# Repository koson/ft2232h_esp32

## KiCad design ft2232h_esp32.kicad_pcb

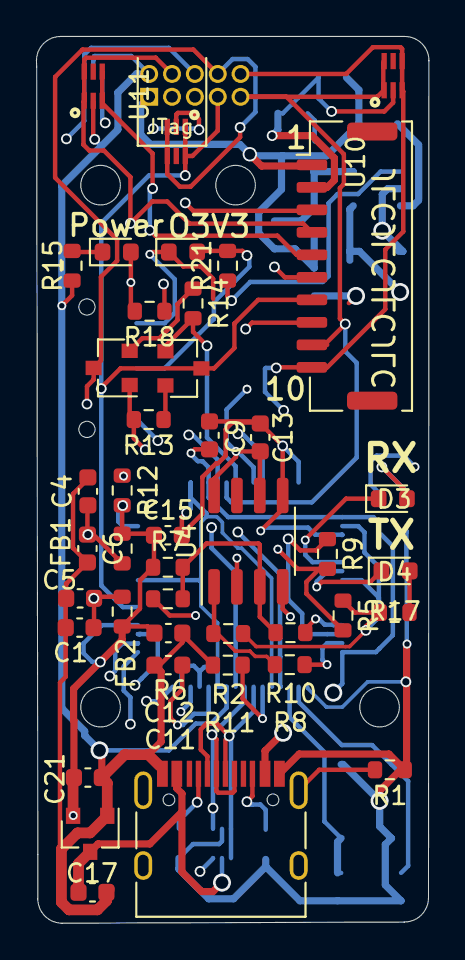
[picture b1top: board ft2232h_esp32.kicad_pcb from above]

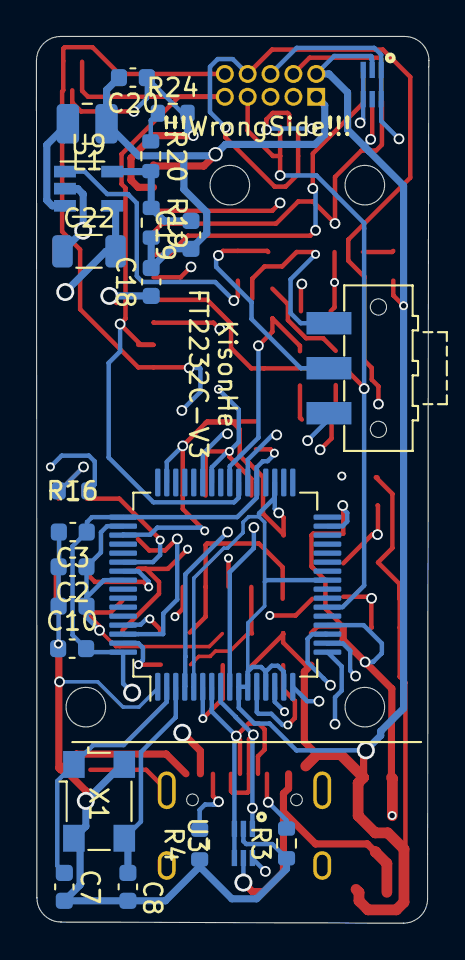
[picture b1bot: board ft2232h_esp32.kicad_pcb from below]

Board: 4 copper layers, 21.8 x 49.3 mm, 70 parts (23 on the bottom side), 46 nets.

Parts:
C1, C2, C3, C4: 4.7uf/25V(10%); C_0603_1608Metric
C5, C6, C9, C10, C11, C12, C13, C14, C15: 0.1uf/25v(10%); C_0603_1608Metric
C7, C8: 20pf; C_0603_1608Metric
C17, C21: 1uf; C_0603_1608Metric
C18, C20: 22uf; C_0603_1608Metric
C19: 22pf; C_0603_1608Metric
C22: 22uf/6.3v; C_1206_3216Metric
D2: POWERLED-Green; LED_0603_1608Metric
D3: BLUELED; LED_0603_1608Metric
D4: REDLED; LED_0603_1608Metric
D5: OUT3V3LED-Yellow; LED_0603_1608Metric
FB1, FB2: 1k@100mhz; R_0603_1608Metric
H1, H2, H3, H4: MountingHole; MountingHole_2.2mm_M2
J1: USB_C_Receptacle_USB2.0; USB_C_Receptacle_HRO_TYPE-C-31-M-12
L1: 2.2uh; L_1008_2520Metric
Q1, Q2: S8050; SOT-23
R1, R24: 0; R_0603_1608Metric
R2, R5, R7: 10k(1%); R_0603_1608Metric
R3, R4: 5.1k; R_0603_1608Metric
R6: 2.2k(1%); R_0603_1608Metric
R8, R9, R10: 33R(1%); R_0603_1608Metric
R11: 12k(1%); R_0603_1608Metric
R12: 1k(1%); R_0603_1608Metric
R13, R14: 100k(1%); R_0603_1608Metric
R15, R21: 10k; R_0603_1608Metric
R16, R17: 2.2k; R_0603_1608Metric
R18: 1k; R_0603_1608Metric
R19: 100k; R_0603_1608Metric
R20: 22k; R_0603_1608Metric
SW1: SW_SPDT; SW_SPDT_CK-JS102011SAQN
U1: ESP32FullConnector; jtag1.27-10
U2: ESP32FullConnector; Molex_CLIK-Mate_502382-1070_1x10-1MP_P1.25mm_Vertical
U3, U10, U11, U12, U13: USBLC6-2SC6-Power_Protection; USBLC6-2P6-SOT666
U4: 93C56-C173182; SOP-8_3.76x4.96mm_P1.27mm
U5: FT2232HL; LQFP-64_10x10mm_P0.5mm
U8: XC6206P332MR; SOT-23
U9: SY8089AAAC; TSOT-23-5
X1: ASCO; Oscillator_SMD_Fordahl_DFAS15-4Pin_5.0x3.2mm

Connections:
3v3OUT: C18.2, C19.1, C20.2, L1.1, R19.2, U1.1, U2.1
2232RX: U1.9, U2.9, U5.39, U10.1, U10.6
2232TX: U1.10, U2.10, U5.38, U10.3, U10.4
+1V8: C3.1, C9.1, C10.1, C11.1, U5.12, U5.37, U5.49, U5.64
+3V3: C2.1, C12.1, C13.1, C14.1, C15.1, C21.2, D2.2, FB1.2, FB2.2, R2.1, R5.1, R7.1, R12.2, R16.1, R17.1, R18.2, U4.6, U4.8, U5.20, U5.31, U5.42, U5.50, U5.56, U8.2
EECLK: R5.2, R9.2, U4.2
EECS: R2.2, R8.2, U4.1
EEDATA: R6.1, R7.2, R10.2, U4.3
GND: C1.2, C2.2, C3.2, C4.2, C5.2, C6.2, C7.2, C8.2, C9.2, C10.2, C11.2, C12.2, C13.2, C14.2, C15.2, C17.1, C18.1, C20.1, C21.1, C22.1, D5.1, J1.A1, J1.A12, J1.B1, J1.B12, R1.1, R3.1, R4.1, R11.2, R15.1, R24.2, SW1.3, U1.2, U2.2, U3.2, U4.5, U5.1, U5.5, U5.10, U5.11, U5.13, U5.15, U5.25, U5.35, U5.47, U5.51, U8.1, U9.2, U10.2, U11.2, U12.2, U13.2, X1.2, X1.4
IO0: Q2.3, U1.8, U2.8, U13.3, U13.4
unnamed: C1.1, C5.1, FB2.1, U5.4
unnamed: C4.1, C6.1, FB1.1, U5.9
unnamed: C7.1, U5.2, X1.1
unnamed: C8.1, U5.3, X1.3
unnamed: C19.2, R19.1, R20.2, U9.5
unnamed: D2.1, R15.2
unnamed: D3.2, R16.2
unnamed: D4.2, R17.2
unnamed: D5.2, R21.2, SW1.2
unnamed: J1.A5, R3.2
unnamed: J1.B5, R4.2
unnamed: J1.S1, R1.2
unnamed: L1.2, U9.3
unnamed: Q1.2, R13.1
unnamed: Q2.2, R14.1
unnamed: R6.2, U4.4
unnamed: R8.1, U5.63
unnamed: R9.1, U5.62
unnamed: R10.1, U5.61
unnamed: R11.1, U5.6
unnamed: R12.1, U5.14
unnamed: R18.1, SW1.1
unnamed: R20.1, R24.1
unnamed: R21.1, U9.1
RXLED: D3.1, U5.54
TCK: U1.3, U2.3, U5.16, U12.3, U12.4
TDI: U1.5, U2.5, U5.17, U11.3, U11.4
TDO: U1.4, U2.4, U5.18, U11.1, U11.6
TMS: U1.6, U2.6, U5.19, U12.1, U12.6
TXLED: D4.1, U5.55
USB_DN: J1.A7, J1.B7, U3.3, U3.4, U5.7
USB_DP: J1.A6, J1.B6, U3.1, U3.6, U5.8
VBUS: C17.2, C22.2, J1.A4, J1.A9, J1.B4, J1.B9, U3.5, U8.3, U9.4
nDTR: Q2.1, R13.2, U5.43
nRTS: Q1.1, R14.2, U5.40
nTRST: Q1.3, U1.7, U2.7, U5.22, U13.1, U13.6
